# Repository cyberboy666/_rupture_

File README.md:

# \_rupture\_

### simple analog video glitch circuit - adapted from a karl klomp design

- this circuit is distributed by __UNDERSCORES__ - _an open video hardware label_ : it is available to purchase - as a pcb, kit or assembled unit - at [underscores.shop](https://underscores.shop/_rupture_/)
- the schematic for the circuit can be found [here](/hardware/schematic.pdf)
- the pcb gerber files for the lastest version can be found [here](/hardware/gerber_latest.zip)
- interactive BOM is [here](https://htmlpreview.github.io/?https://github.com/cyberboy666/_rupture_/blob/main/hardware/bom/ibom.html)
- consider [donating](https://opencollective.com/underscores) to the underscores project to help us continue creating for the commons
## description

this circuit takes any composite video signal as input and destroys the signal in many interesting and unpredictable ways - due to the nature of analog video glitches for best results you should output this signal directly to a crt tv.

## demo video

## background

<details><summary>background</summary>
  
this project is an adaption of a video glitch processing circuit created orginally by [Karl Klomp](https://www.karlklomp.nl/) known as __the rupter__. this and many other interesting historic video hardware glitch machines can be seen on [web-archive](https://web.archive.org/web/20150206171254/https://www.karlklomp.nl/) of their site. pictures, schematic and videos of the original circuit are below:

my adaption of it started as an exercise in my [_intro to kicad_](https://github.com/cyberboy666/kicad_video_workshop) workshop for VIDICON_2020 - i ended up getting the boards fab'd and found it to be a very useful device in my studio - worthy of sharing futher!
  
</details>

# documentation

this project is fully _open-source hardware_ - all the files required to build it are included in this repo for free. if you have the time and/or skill you can contribute back by collaborating on / testing new designs, improving these docs, making demo videos/other creative content etc. you can also support the project financially by [donating directing](https://opencollective.com/underscores), or purchasing through the [web shop](https://underscores.shop).

depending on whether you are going fully diy or buying an assembled and tested unit, some of the following guides will be relavent to you. the flow would be:

## ordering parts

<details><summary><b>parts sourcing guide (w/ notes on pcb fabracation )</b> - start here if you are building fully from scatch or have purchased a pcb</summary>

i try to source all the parts i can from either:
- [tayda](https://www.taydaelectronics.com/) ; cheaper for common parts like resistors etc, also good for mechanical parts like switches and buttons
- [mouser](https://www.mouser.de/) ; has lots more options, speciality video ic's, can sometimes cost more (free shipping on orders over 50euros)
- other ; ocationally there will be parts which will need to be sourced elsewhere - usaully either aliexpress, ebay or amazon etc...

take a look at the [full_bom](/hardware/bom/full_bom.csv) for this project to see where i am sourcing each part from

## omitting parting
  
if you know you will only power _rupture_ with a 5v supply then the __regulator__ part of the circuit (c7, c8, r1, r2, u1, sw9) can be omitted - just connect the middle and left pins on the sw9 footprint with a resistor leg to permanently select 5v power by-pass.
  
also the values of capicitors on the glitch switches (c1-6) can be customised - i find smaller values are more interesting than larger ones.
  
## import into tayda

- go to the [tayda quick order](https://www.taydaelectronics.com/quick-order/) and in bottom corner choose _add from file_
- select the file [tayda_bom.csv](./hardware/bom/tayda_bom.csv) in the BOM folder (you will have to download it first or clone this repo)
- after importing select _add to cart_
- __NOTE:__ the minimum value for resistors is 10, so you may need to modify these values to add to cart (or if they are already modified here you will need to see the  full_bom for actual part QTY) 

- OPTIONAL: it is a good idea to add some dip-ic sockets and 2.54pin headers/sockets to your tayda order if you dont have them around already
  
## import into mouser

- go to [mouser bom tool](https://nz.mouser.com/Bom/) and click _upload spreadsheet_
- select the file [mouser_bom.csv](./hardware/bom/mouser_bom.csv) in this folder (you will have to download it first or clone this repo), then _upload my spreadsheet_ and _next_
- ensure that __Mouser Part Number__ is selected in the dropdown above the first row, then _next_, _process_
- if everything looks correct can now put _add to basket_

# ordering pcbs

you can support this project by buying individual pcbs from the [shop](https://underscores.shop). if you would rather have pcbs fabricated from gerbers directly the file you need is [here](/hardware/gerber_latest.zip) 

- i get my pcbs fabricated from [jlcpcb](https://cart.jlcpcb.com/quote) - 5 is the minumum order per design
- upload the zip file with the `add gerber file` button
- the default settings are mostly fine - set the __PCB Qty__ and __PCB Color__ settings (you can check that the file looks correct with pcb veiwer)
- it may be best to combine orders with other pcbs you want to have fab'd since the shipping can cost more than the items - also orginising group buys is a good way to distribute the extra pcbs /costs 
  
i often use jlcpcb because they are reliable, cheap and give you an option of colours. remember though that the cheapest Chinese fab houses are not always the most ethical or environmently friendly - if you can afford it consider supporting local companies. 

</details>

## assembly guide

<details><summary><b>assembly guide</b> - start here if you have purchased a diy kit</summary>

## interactive BOM for build guiding

follow this link to view the [interactive BOM](https://htmlpreview.github.io/?https://github.com/cyberboy666/_rupture_/blob/main/hardware/bom/ibom.html)

## general solder advices

- remember to heat pad first (2-3seconds), then add solder, then continue to heat (1-2seconds)

- Checkout the web-comic [soldering is easy](https://mightyohm.com/files/soldercomic/FullSolderComic_EN.pdf) for more soldering advice

## general order of assembly

- in general while assembling i start placing resistors and capacitors first. placing 5 - 10 components at a time and then flipping the board to solder them and trim the legs etc.
- next i would do diodes, transistors and ic's - taking care that these are placed in the right direction (using a ic socket can be useful)
- finally i place the interface parts - rca jacks, power jack, pots and switches - make sure these have lots of solder on for structural stablity

## specific assembly advice

- start with the ic if you going for smd part - remember to orient it correctly (follow arrow on silkscreen) - can check connection with multimeter by using the dip pads
- next place resistors and capicators - can also do regulator...
- now place the switches - make sure enough solder is on the outer pins for structural stability
- barrel and rca jacks next
- and finally the pots
  
</details>
  
## operating guide
  
<details><summary><b>operating guide</b> - start here if you have purchased an assembled unit</summary>

### setup
  
start by connecting a composite video source to the IN rca jack and a composite video display to the OUT rca jack (use a crt tv for best results) - now without the power plugged in you should be able to see your clean video source on the display by changing the ROUTER switches to both UP or both DOWN
  
### router
  
the video input and video output signals can be connected to the effect circuit in 4 different ways - this is because the left router switch will connect the IN signal to the TOP/BOTTOM of the effect circuit, and the right router switch will connect the OUT signal to the TOP/BOTTOM - without power TOP-TOP and BOTTOM-BOTTOM acts as straight signal pass-through. with power these will give different effects.
  
### regulator
  
the REGULATOR switch next to the power jack selects whether the power line is passed through a ~7v voltage regulator -> if you are powering your circuit with 9-12v then you must have this switched on (RIGHT) to avoid damaging your ic. if you are powering with 5v then it can be bypassed by switching to the left, although it wont hurt to still have it on - just changes the effects slightly in some places.
  
### glitch controls
  
the 4 knobs and 6 switches will control the glitch effects when the power is connected. the default position is all knobs rotated anti-clockwise and all glitch switches set to UP. in general i would start by moving the left most knob first and working towards the right most - same with the glitch switches.
  
ROUTER positions UP-UP, DOWN-DOWN and DOWN-UP all produce quite interesting and different glitches on a crt screen. UP-DOWN for the most part does little more than a few abstract lines.
  
</details>

### more info

<details><summary><b>how the circuit works</b></summary>
  
[coming soon]
                                                                                                                             
</details>

<details><summary><b>contributing guide</b></summary>
  
if you would like to contribute back to these projects in some way but dont know how the best thing (for now) would be to reach out to me directly ( tim@cyberboy666.com or @cyberboy666 on scanlines forum) - i will be happy to help
  
</details>

## credits & more info

This circuit is distributed through UNDERSCORES – open video hardware label – visit [underscores.shop](https://underscores.shop) for more info

The pcb was designed using KICAD

Everything from gerbers, cad files, panels and documentation is freely available online and distributed under CC-BY-SA / open-source licenses – help us contribute to the commons !

Ask any questions or start discussions related to this project on the [scanlines.xyz](https://scanlines.xyz) forum – an online community space dedicated to diy av / electronic media art

You can contact me directly at tim (at) cyberboy666 (dot) com 
Please get in touch if you are interested in hosting a workshop !

thanks to Karl Klomp for inpiring me and so many others, to Bastien Lavaud for circuit advice, always. To Ben Caldwell for project advice. To everyone who has or will contribute ♥♥♥

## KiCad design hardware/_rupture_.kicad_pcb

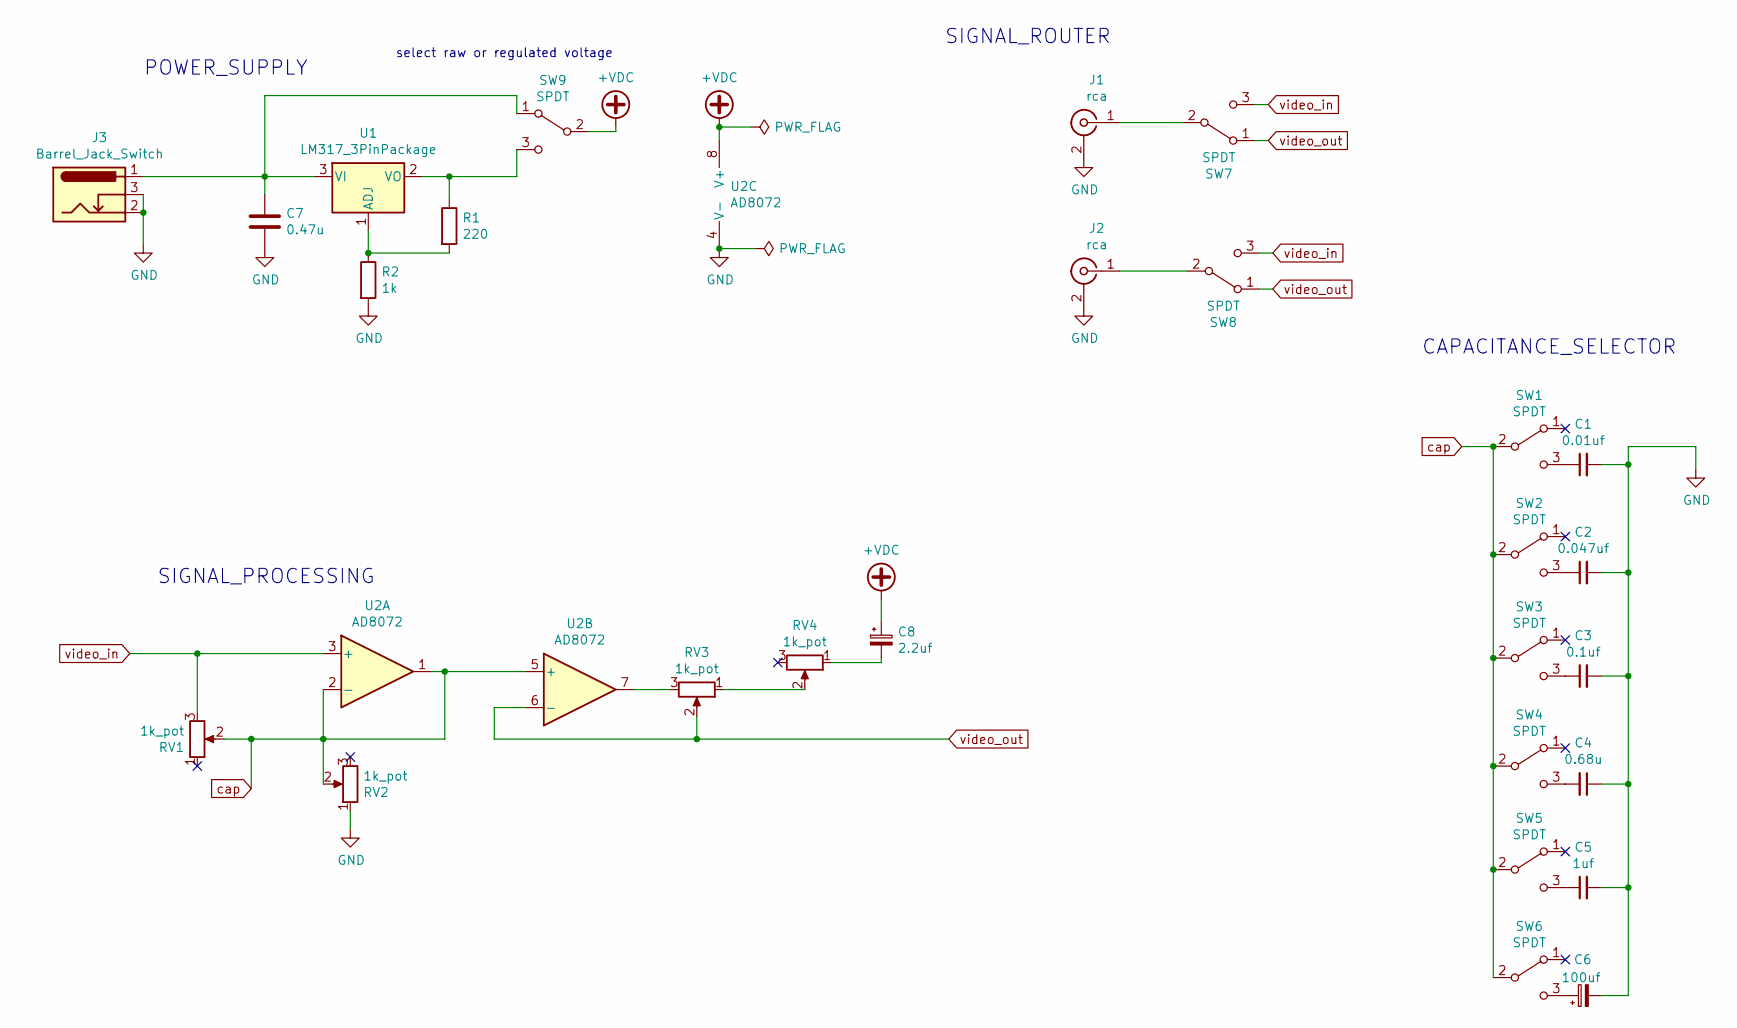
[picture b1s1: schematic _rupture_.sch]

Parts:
C1: 0.01uf; C_Disc_D4.7mm_W2.5mm_P5.00mm
C2: 0.047uf; C_Disc_D4.7mm_W2.5mm_P5.00mm
C3: 0.1uf; C_Disc_D4.7mm_W2.5mm_P5.00mm
C4: 0.68u; C_Disc_D4.7mm_W2.5mm_P5.00mm
C5: 1uf; C_Disc_D4.7mm_W2.5mm_P5.00mm
C6: 100uf; CP_Radial_D5.0mm_P2.50mm
C7: 0.47u; C_Disc_D4.7mm_W2.5mm_P5.00mm
C8: 2.2uf; CP_Radial_D5.0mm_P2.50mm
J1, J2: rca; tht_rca_vertical
J3: Barrel_Jack_Switch; BarrelJack_Horizontal
R1: 220; R_Axial_DIN0207_L6.3mm_D2.5mm_P7.62mm_Horizontal
R2: 1k; R_Axial_DIN0207_L6.3mm_D2.5mm_P7.62mm_Horizontal
RV1, RV2, RV3, RV4: 1k_pot; pot_vertical_9mm
SW1, SW2, SW3, SW4, SW5, SW6, SW7, SW8, SW9: SPDT; spdt_slide_switch_small_tayda
U1: LM317_3PinPackage; TO-92L_HandSolder
U2: AD8072; DIP-SOIC-8

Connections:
+VDC: C8.1, SW9.2 (B), U2.8 (V+)
GND: C1.2, C2.2, C3.2, C4.1, C5.2, C6.2, C7.2, J1.2 (Ext), J2.2 (Ext), J3.2, J3.3, R2.2, RV2.1, U2.4 (V-)
unnamed: C1.1, SW1.3 (C)
unnamed: C2.1, SW2.3 (C)
unnamed: C3.1, SW3.3 (C)
unnamed: C4.2, SW4.3 (C)
unnamed: C5.1, SW5.3 (C)
unnamed: C6.1, SW6.3 (C)
unnamed: C7.1, J3.1, SW9.1 (A), U1.3 (VI)
unnamed: C8.2, RV4.1
unnamed: J1.1 (In), SW7.2 (B)
unnamed: J2.1 (In), SW8.2 (B)
unnamed: R1.1, SW9.3 (C), U1.2 (VO)
unnamed: R1.2, R2.1, U1.1 (ADJ)
unnamed: RV3.1, RV4.2
unnamed: RV3.3, U2.7
cap: RV1.2, RV2.2, SW1.2 (B), SW2.2 (B), SW3.2 (B), SW4.2 (B), SW5.2 (B), SW6.2 (B), U2.1, U2.2 (-), U2.5 (+)
video_in: RV1.3, SW7.3 (C), SW8.3 (C), U2.3 (+)
video_out: RV3.2, SW7.1 (A), SW8.1 (A), U2.6 (-)

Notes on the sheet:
POWER_SUPPLY
SIGNAL_PROCESSING
SIGNAL_ROUTER
CAPACITANCE_SELECTOR
select raw or regulated voltage

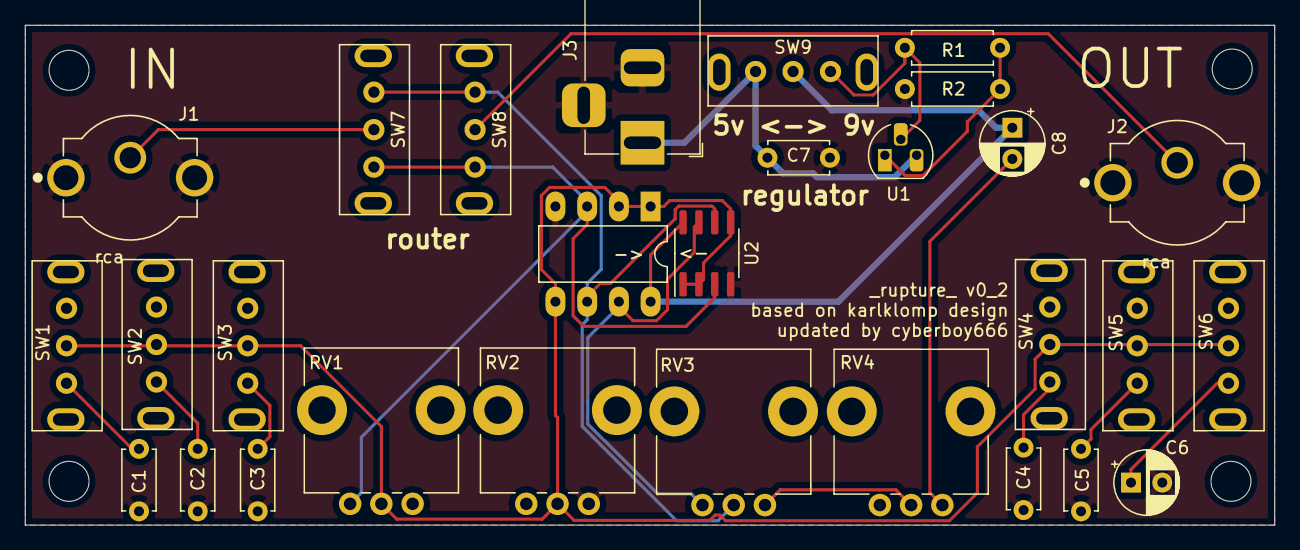
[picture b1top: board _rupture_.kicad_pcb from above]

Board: 2 copper layers, 100.0 x 40.0 mm, 28 parts (0 on the bottom side), 19 nets.

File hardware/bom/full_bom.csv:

sku,qty,ref,val,vendor
A-962,1,C1 ,0.01uf,tayda
A-552,1,C2 ,0.047uf,tayda
A-4008,1,C3 ,0.1uf,tayda
A-1482,1,C4 ,0.68u,tayda
A-321,1,C5 ,1uf,tayda
A-1063,1,C6 ,100uf,tayda
A-142,1,C7 ,0.47u,tayda
A-4510,1,C8 ,2.2uf,tayda
490-RCJ-024,2,J1 J2 ,rca,mouser
A-4118,1,J3 ,Barrel_Jack_Switch,tayda
A-2246,1,R1 ,220,tayda
A-2200,1,R2 ,1k,tayda
A-1863,4,RV1 RV2 RV3 RV4 ,1k_pot,tayda
A-659,9,SW1 SW2 SW3 SW4 SW5 SW6 SW7 SW8 SW9 ,SPDT,tayda
A-500,1,U1 ,LM317_3PinPackage,tayda
584-AD8072JNZ,1,U2 ,AD8072,mouser

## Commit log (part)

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2021-07-19 firsr commit
2022-02-22 latest circuit revision
2022-02-22 rename kicad files
2022-02-28 update bom
2022-03-22 finish booklet
2022-03-22 file typo
2023-07-12 update with panels
2024-05-19 adding git attributes
